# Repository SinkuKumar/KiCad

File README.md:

# KiCad
My electronics hadware projects here

1. [My first project](https://github.com/SinkuKumar/KiCad/tree/main/First_Project)
2. [LDR circuit for arduino boards](https://github.com/SinkuKumar/KiCad/tree/main/LDR_Circuit)

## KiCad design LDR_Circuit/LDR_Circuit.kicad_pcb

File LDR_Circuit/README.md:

# LDR Circuit

A simple LDR sensor circuit to use with arduino boards.

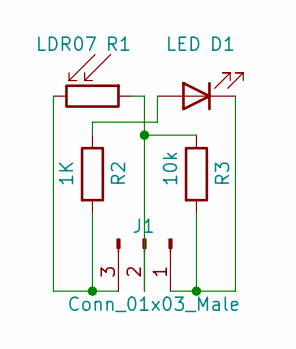
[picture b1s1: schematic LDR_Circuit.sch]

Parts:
D1: LED; LED_D3.0mm_FlatTop
J1: Conn_01x03_Male; PinHeader_1x03_P1.00mm_Vertical
R1: LDR07; PinHeader_1x03_P1.00mm_Vertical
R2: 1K; R_Axial_DIN0204_L3.6mm_D1.6mm_P7.62mm_Horizontal
R3: 10k; R_Axial_DIN0204_L3.6mm_D1.6mm_P7.62mm_Horizontal

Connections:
unnamed: D1.1 (K), J1.1, R3.2
unnamed: D1.2 (A), R2.1
unnamed: J1.2, R1.1, R3.1
unnamed: J1.3, R1.2, R2.2

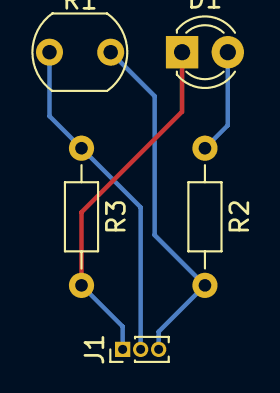
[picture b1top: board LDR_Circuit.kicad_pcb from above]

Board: 2 copper layers, 5 parts (0 on the bottom side), 4 nets.

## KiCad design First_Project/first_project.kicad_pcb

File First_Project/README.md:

## My first KiCad Project:
Driving an LED using a resistor and 9v battery.

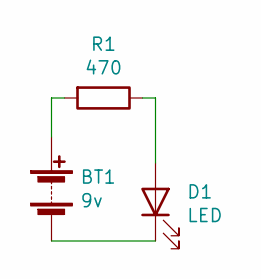
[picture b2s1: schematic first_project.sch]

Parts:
BT1: 9v; Harwin_LTek-Male_02_P2.00mm_Vertical
D1: LED; LED_D5.0mm_Clear
R1: 470; R_Axial_DIN0617_L17.0mm_D6.0mm_P30.48mm_Horizontal

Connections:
unnamed: BT1.1 (+), R1.2
unnamed: BT1.2 (-), D1.1 (K)
unnamed: D1.2 (A), R1.1

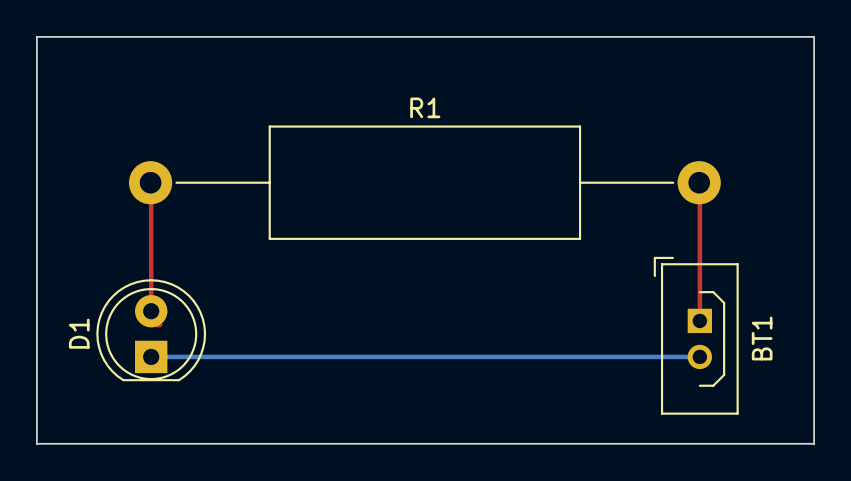
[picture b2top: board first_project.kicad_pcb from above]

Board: 2 copper layers, 43.2 x 22.6 mm, 3 parts (0 on the bottom side), 3 nets.

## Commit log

2021-05-29 Add project files
2021-05-29 Add gif
    Add gif for 3d schematic demo
2021-05-31 Add LDR_Circuit.gif
2021-05-31 Add files
